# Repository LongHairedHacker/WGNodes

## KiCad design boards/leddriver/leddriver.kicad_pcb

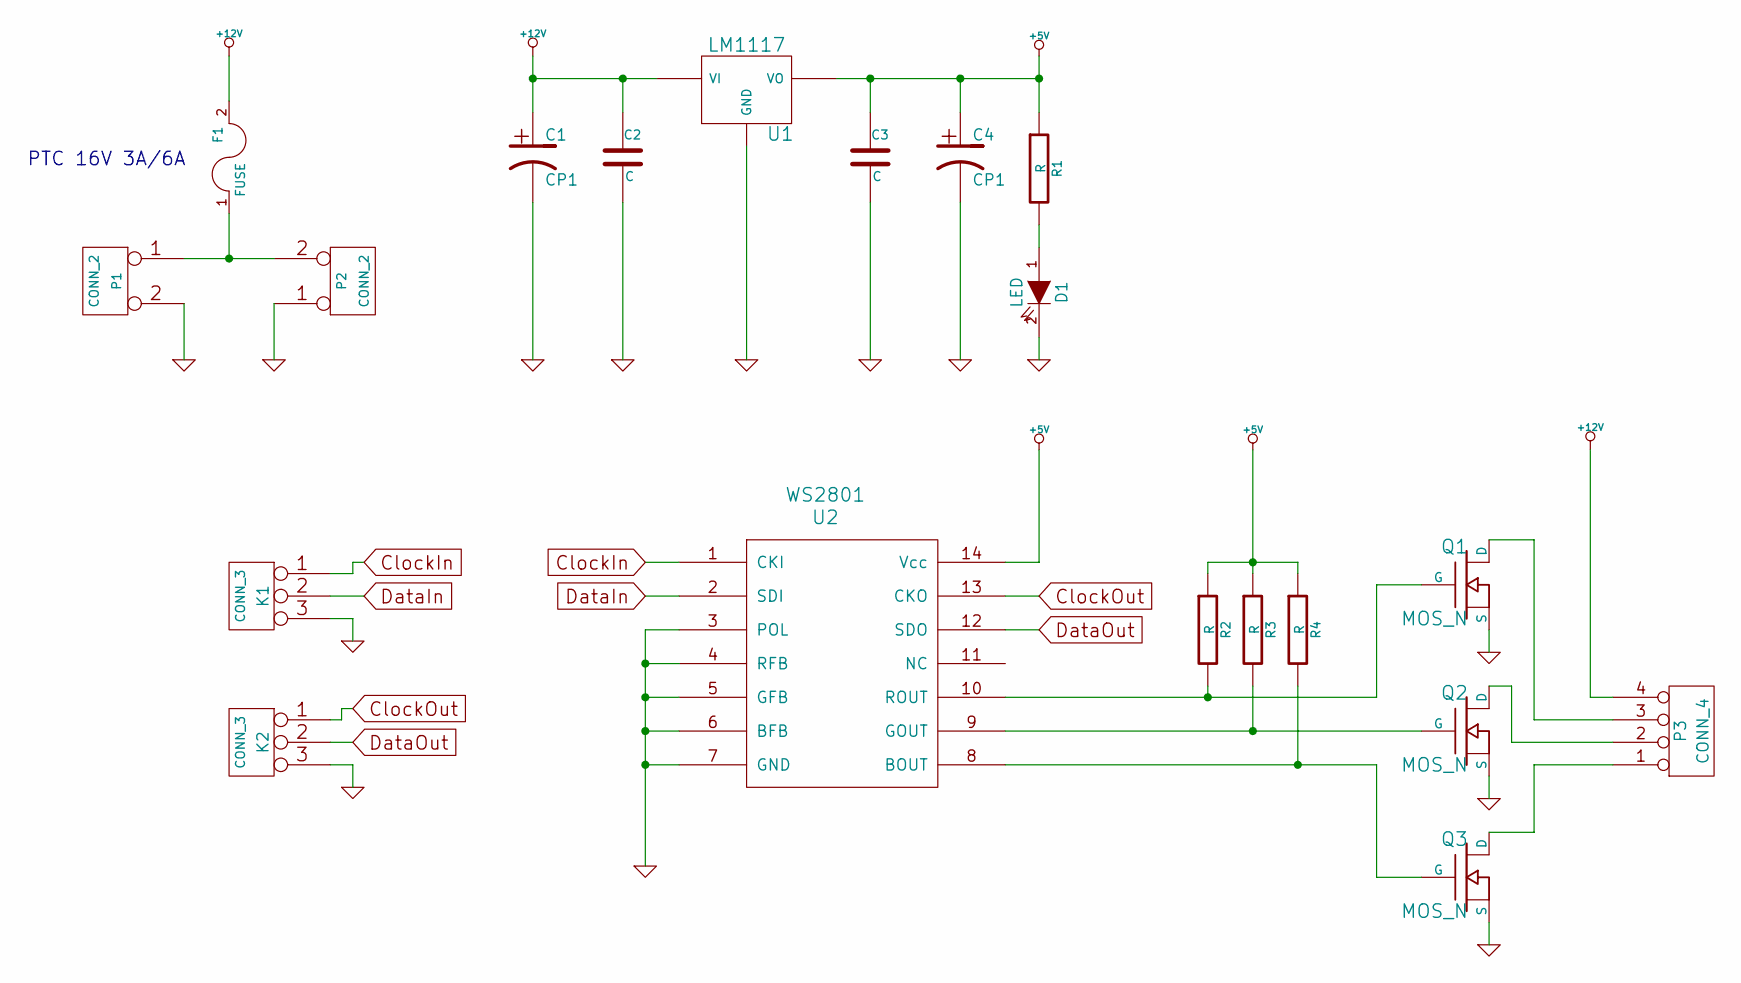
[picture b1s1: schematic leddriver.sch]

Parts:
C1, C4: CP1
C2, C3: C
D1: LED
F1: FUSE
K1, K2: CONN_3
P1, P2: CONN_2
P3: CONN_4
Q1, Q2, Q3: MOS_N
R1, R2, R3, R4: R
U1: LM1117
U2: WS2801

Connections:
+5V: C3.1, C4.1, R1.1, R2.1, R3.1, R4.1, U1.2 (VO), U2.14 (Vcc)
+12V: C1.1, C2.1, F1.2, P3.4, U1.3 (VI)
ClockIn: K1.1, U2.1 (CKI)
ClockOut: K2.1, U2.13 (CKO)
DataIn: K1.2 (PM), U2.2 (SDI)
DataOut: K2.2 (PM), U2.12 (SDO)
GND: C1.2, C2.2, C3.2, C4.2, D1.2 (K), K1.3, K2.3, P1.2 (PM), P2.1, Q1.S, Q2.S, Q3.S, U1.1 (GND), U2.3 (POL), U2.4 (RFB), U2.5 (GFB), U2.6 (BFB), U2.7 (GND); also elsewhere on the board
unnamed: P3.1, Q3.D
unnamed: Q3.G, R4.2, U2.8 (BOUT)
unnamed: Q1.G, R2.2, U2.10 (ROUT)
unnamed: P3.3, Q1.D
unnamed: P3.2, Q2.D
unnamed: F1.1, P1.1, P2.2 (PM)
unnamed: D1.1 (A), R1.2
unnamed: Q2.G, R3.2, U2.9 (GOUT)

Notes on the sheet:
PTC 16V 3A/6A

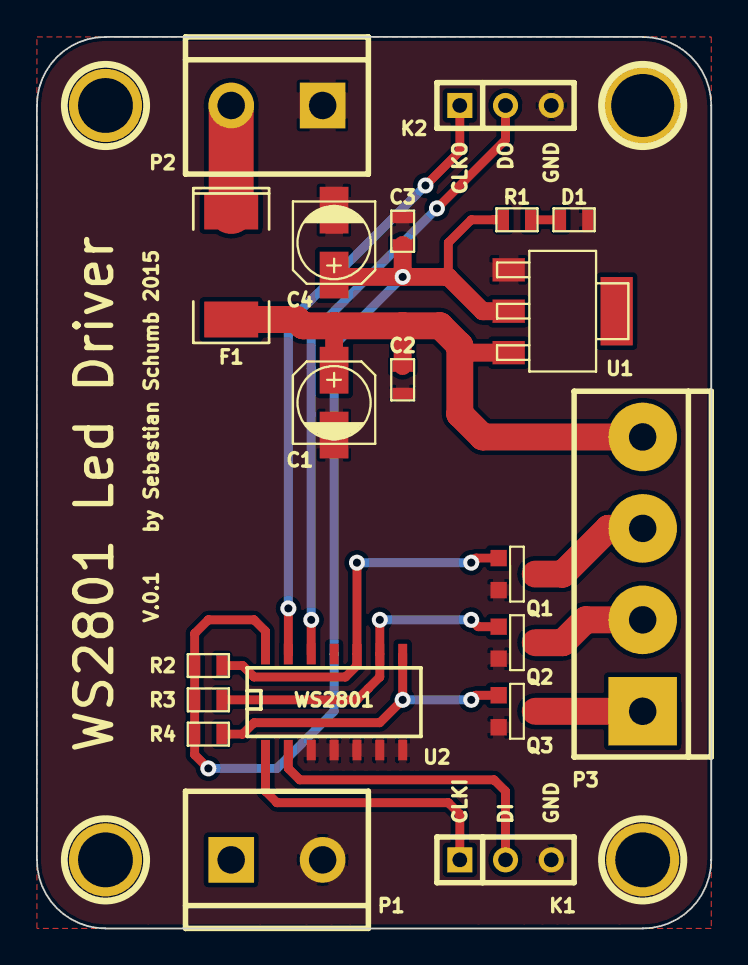
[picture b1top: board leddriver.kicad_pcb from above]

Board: 2 copper layers, 37.5 x 49.5 mm, 24 parts (0 on the bottom side), 15 nets.

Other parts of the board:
1PIN, 1PIN#2, 1PIN#3, 1PIN#4: P***; 1pin

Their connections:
GND: 1PIN.1, 1PIN#2.1; also elsewhere on the board

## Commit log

2015-05-26 Finalized Silkscreen Generated gerbers for production
2015-08-26 Timers are cooler than loops
2015-08-28 Added code for mqtt
